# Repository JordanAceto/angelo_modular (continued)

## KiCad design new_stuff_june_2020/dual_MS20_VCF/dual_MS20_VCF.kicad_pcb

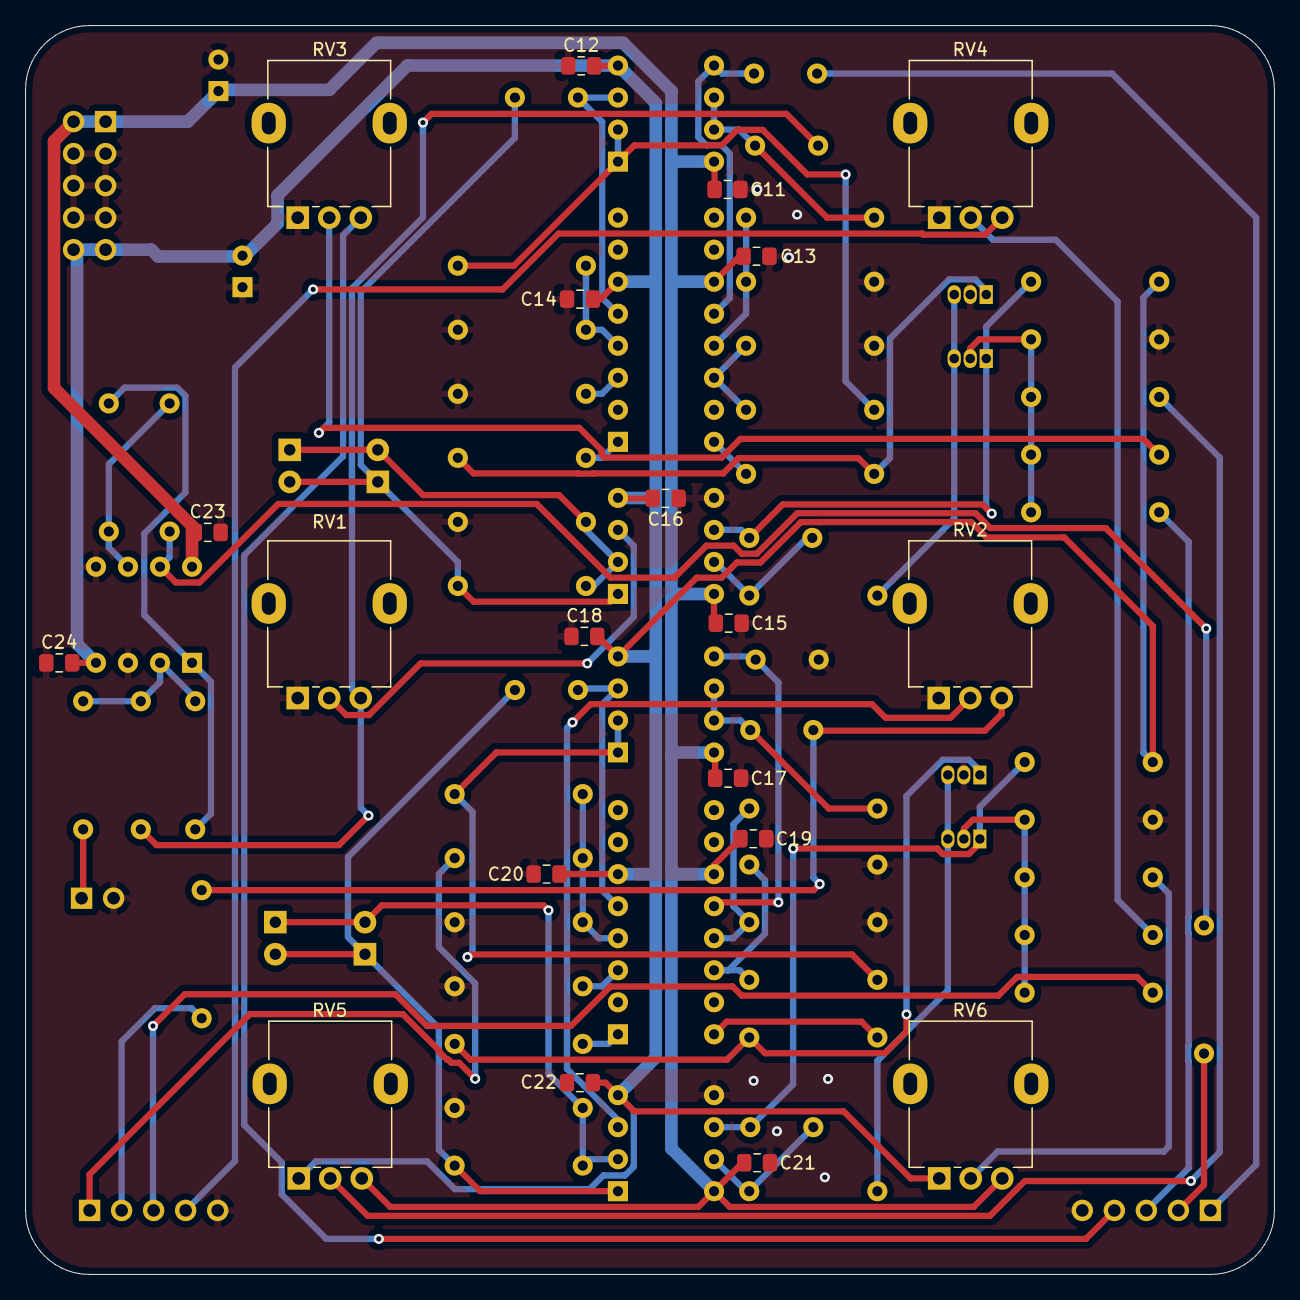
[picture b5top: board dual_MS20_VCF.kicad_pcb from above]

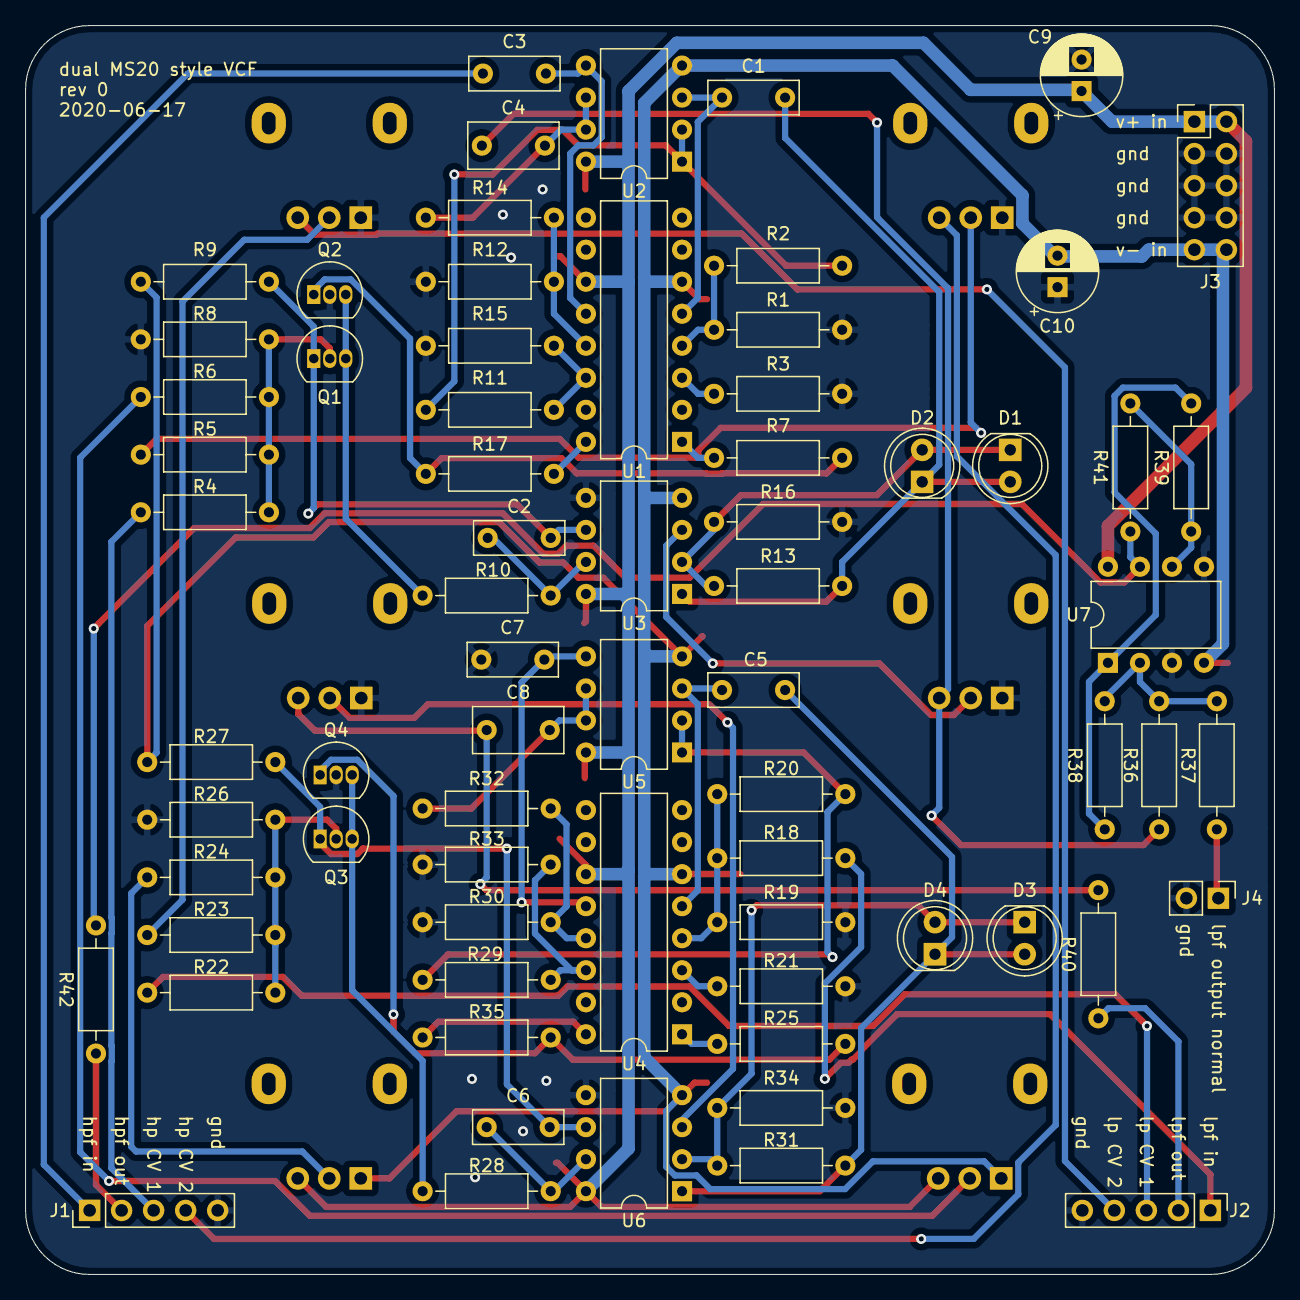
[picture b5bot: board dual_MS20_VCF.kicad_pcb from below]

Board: 2 copper layers, 99.1 x 99.1 mm, 91 parts (71 on the bottom side), 58 nets.

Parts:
C1, C3, C5, C7: 1nF; C_Rect_L7.0mm_W2.5mm_P5.00mm
C2, C6: 4n7; C_Rect_L7.0mm_W2.5mm_P5.00mm
C4, C8: 470nF; C_Rect_L7.0mm_W3.5mm_P5.00mm
C9, C10: 10uF; CP_Radial_D6.3mm_P2.50mm
C11, C12, C13, C14, C15, C16, C17, C18, C19, C20, C21, C22, C23, C24: 100nF; C_0805_2012Metric_Pad1.15x1.40mm_HandSolder
D1, D2, D3, D4: green; LED_D5.0mm
J1, J2: Conn_01x05; PinHeader_1x05_P2.54mm_Vertical
J3: power_in; PinHeader_2x05_P2.54mm_Vertical
J4: lpf_output_normal; PinHeader_1x02_P2.54mm_Vertical
Q1, Q2, Q3, Q4: BC558; TO-92_Inline
R1, R3, R12, R15, R19, R21, R30, R33: 220; R_Axial_DIN0207_L6.3mm_D2.5mm_P10.16mm_Horizontal
R2, R7, R11, R13, R14, R17, R18, R20, R25, R29, R31, R32, R35: 10k; R_Axial_DIN0207_L6.3mm_D2.5mm_P10.16mm_Horizontal
R4, R5, R6, R22, R23, R24, R36, R37, R38, R39, R41: 100k; R_Axial_DIN0207_L6.3mm_D2.5mm_P10.16mm_Horizontal
R8, R16, R26, R34: 1k8; R_Axial_DIN0207_L6.3mm_D2.5mm_P10.16mm_Horizontal
R9, R27: 470k; R_Axial_DIN0207_L6.3mm_D2.5mm_P10.16mm_Horizontal
R10, R28: 4k7; R_Axial_DIN0207_L6.3mm_D2.5mm_P10.16mm_Horizontal
R40, R42: 1k; R_Axial_DIN0207_L6.3mm_D2.5mm_P10.16mm_Horizontal
RV1, RV2, RV3, RV4, RV5, RV6: 100k; Potentiometer_Alpha_RD901F-40-00D_Single_Vertical
U1, U4: LM13700; DIP-16_W7.62mm
U2, U3, U5, U6: MC1458; DIP-8_W7.62mm
U7: TL072; DIP-8_W7.62mm

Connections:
+12V: C9.1, C11.1, C13.1, C15.1, C17.1, C19.1, C21.1, C23.1, J3.1, J3.2, RV5.3, RV6.3, U1.11, U2.8, U3.8, U4.11, U5.8, U6.8, U7.8
-12V: C10.2, C12.2, C14.2, C16.2, C18.2, C20.2, C22.2, C24.2, J3.9, J3.10, R9.2, R27.2, RV5.1, RV6.1, U1.6, U2.4, U3.4, U4.6, U5.4, U6.4, U7.4
/HPF/hpf_cv_in_1: J1.3, R4.2
/HPF/hpf_cv_in_2: R5.2, RV3.2
/HPF/hpf_cv_in_3: R6.2, RV5.2
/HPF/hpf_in: C3.2, J1.1
/HPF/i_out: Q2.1, R7.1, R17.1
/LPF/i_out: Q4.1, R25.1, R35.1
/LPF/lpf_cv_in_1: J2.3, R22.2
/LPF/lpf_cv_in_2: R23.2, RV4.2
/LPF/lpf_cv_in_3: R24.2, RV6.2
/LPF/lpf_in: J2.1, R18.2
/LPF/lpf_out: C8.1, R40.2, RV2.3
/high_pass: C4.1, R36.2, RV1.3
/low_pass: J2.2, R40.1
/summed_hp_lp: J1.2, R42.1
GND: C7.2, C9.2, C10.1, C11.2, C12.1, C13.2, C14.1, C15.2, C16.1, C17.2, C18.1, C19.2, C20.1, C21.2, C22.1, C23.2, C24.1, J1.5, J2.5, J3.3, J3.4, J3.5, J3.6, J3.7, J3.8, J4.2, Q2.2, Q4.2, R1.2, R3.2, R8.2, R12.2, R15.2, R16.2, R19.2, R21.2, R26.2, R30.2, R33.2, R34.2, RV1.1, RV2.1, RV3.1, RV4.1, U3.5, U6.5, U7.3, U7.5
unnamed: C1.1, U1.5, U2.3
unnamed: C1.2, D1.2, D2.1, R13.2, U3.1
unnamed: C2.1, R10.1, U3.7
unnamed: C2.2, Q1.1, R9.1, U3.6
unnamed: C3.1, U1.12, U2.5
unnamed: C4.2, R14.1, U2.6, U2.7
unnamed: C5.1, U4.5, U5.3
unnamed: C5.2, D3.2, D4.1, R31.2, U6.1
unnamed: C6.1, R28.1, U6.7
unnamed: C6.2, Q3.1, R27.1, U6.6
unnamed: C7.1, U4.12, U5.5
unnamed: C8.2, R32.1, U5.6, U5.7
unnamed: D1.1, D2.2, R13.1, R16.1, U3.2
unnamed: D3.1, D4.2, R31.1, R34.1, U6.2
unnamed: J1.4, RV3.3
unnamed: J2.4, RV4.3
unnamed: J4.1, R37.2
unnamed: Q1.2, R4.1, R5.1, R6.1, R8.1
unnamed: Q1.3, Q2.3, R10.2
unnamed: Q3.2, R22.1, R23.1, R24.1, R26.1
unnamed: Q3.3, Q4.3, R28.2
unnamed: R1.1, R2.2, U1.4
unnamed: R3.1, U1.3
unnamed: R7.2, U1.1
unnamed: R11.1, R15.1, U1.14
unnamed: R2.1, R11.2, U2.1, U2.2
unnamed: R12.1, R14.2, U1.13
unnamed: R17.2, U1.16
unnamed: R18.1, R19.1, R20.2, U4.4
unnamed: R20.1, R29.2, U5.1, U5.2
unnamed: R21.1, U4.3
unnamed: R25.2, U4.1
unnamed: R29.1, R33.1, U4.14
unnamed: R30.1, R32.2, U4.13
unnamed: R35.2, U4.16
unnamed: R36.1, R37.1, R38.2, U7.2
unnamed: R38.1, R39.2, U7.1
unnamed: R39.1, R41.2, U7.6
unnamed: R41.1, R42.2, U7.7
unnamed: RV1.2, U3.3
unnamed: RV2.2, U6.3

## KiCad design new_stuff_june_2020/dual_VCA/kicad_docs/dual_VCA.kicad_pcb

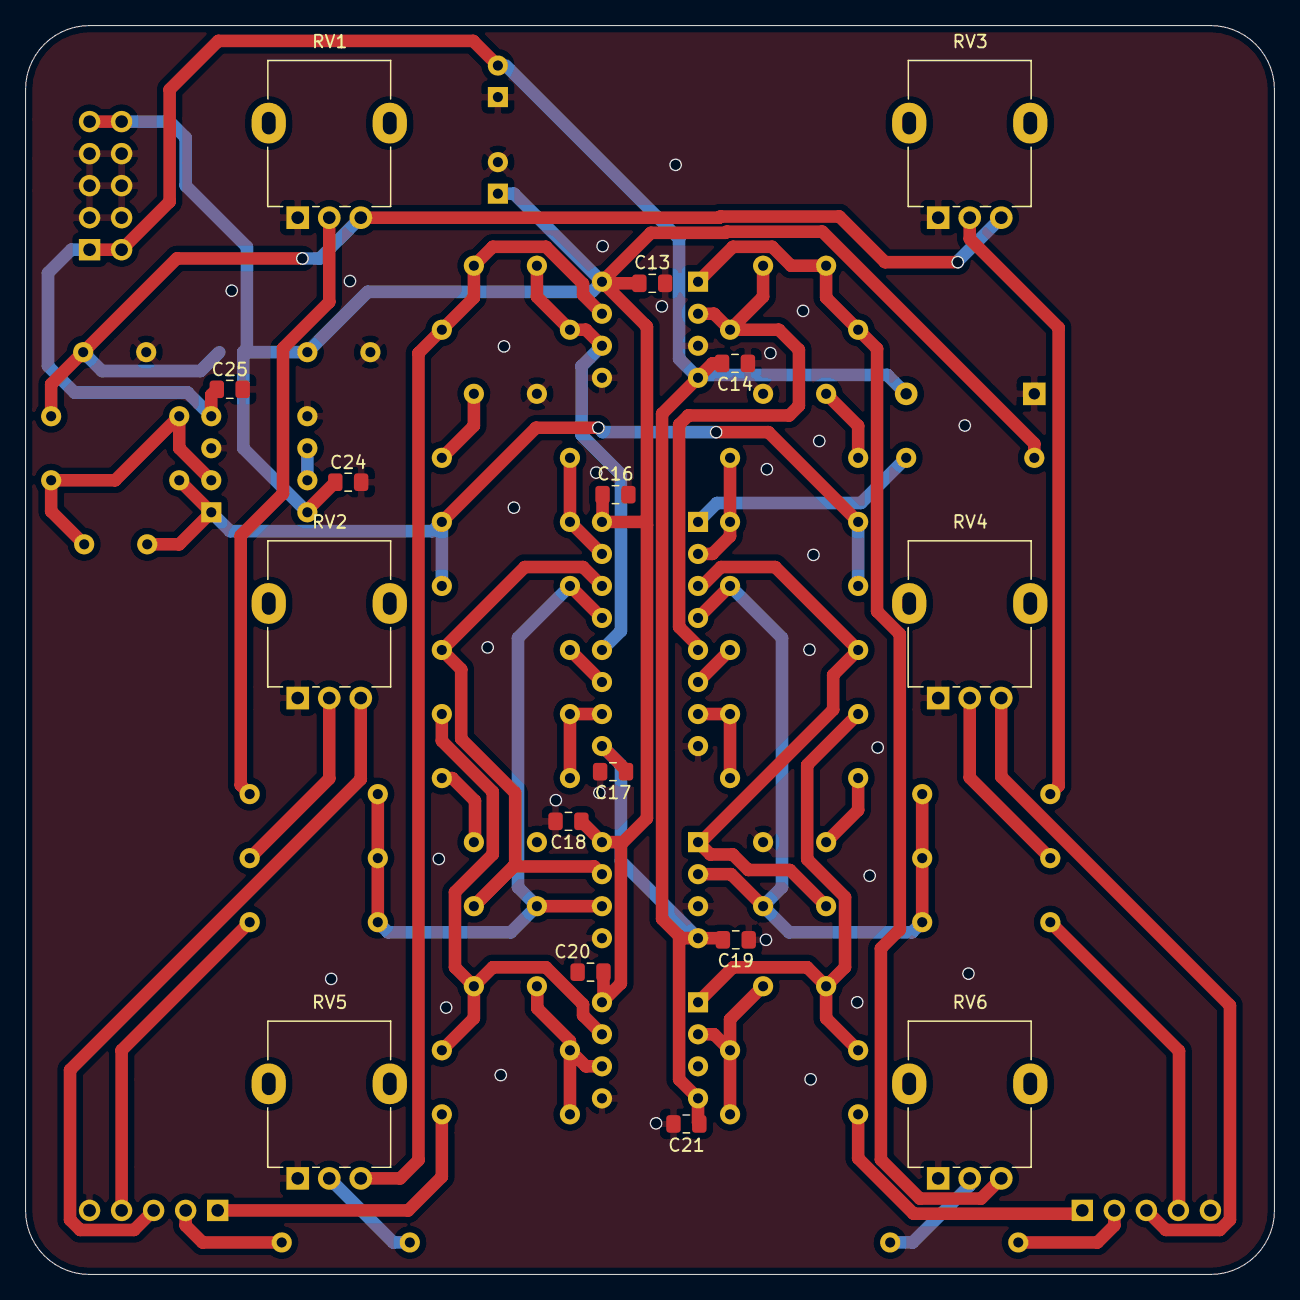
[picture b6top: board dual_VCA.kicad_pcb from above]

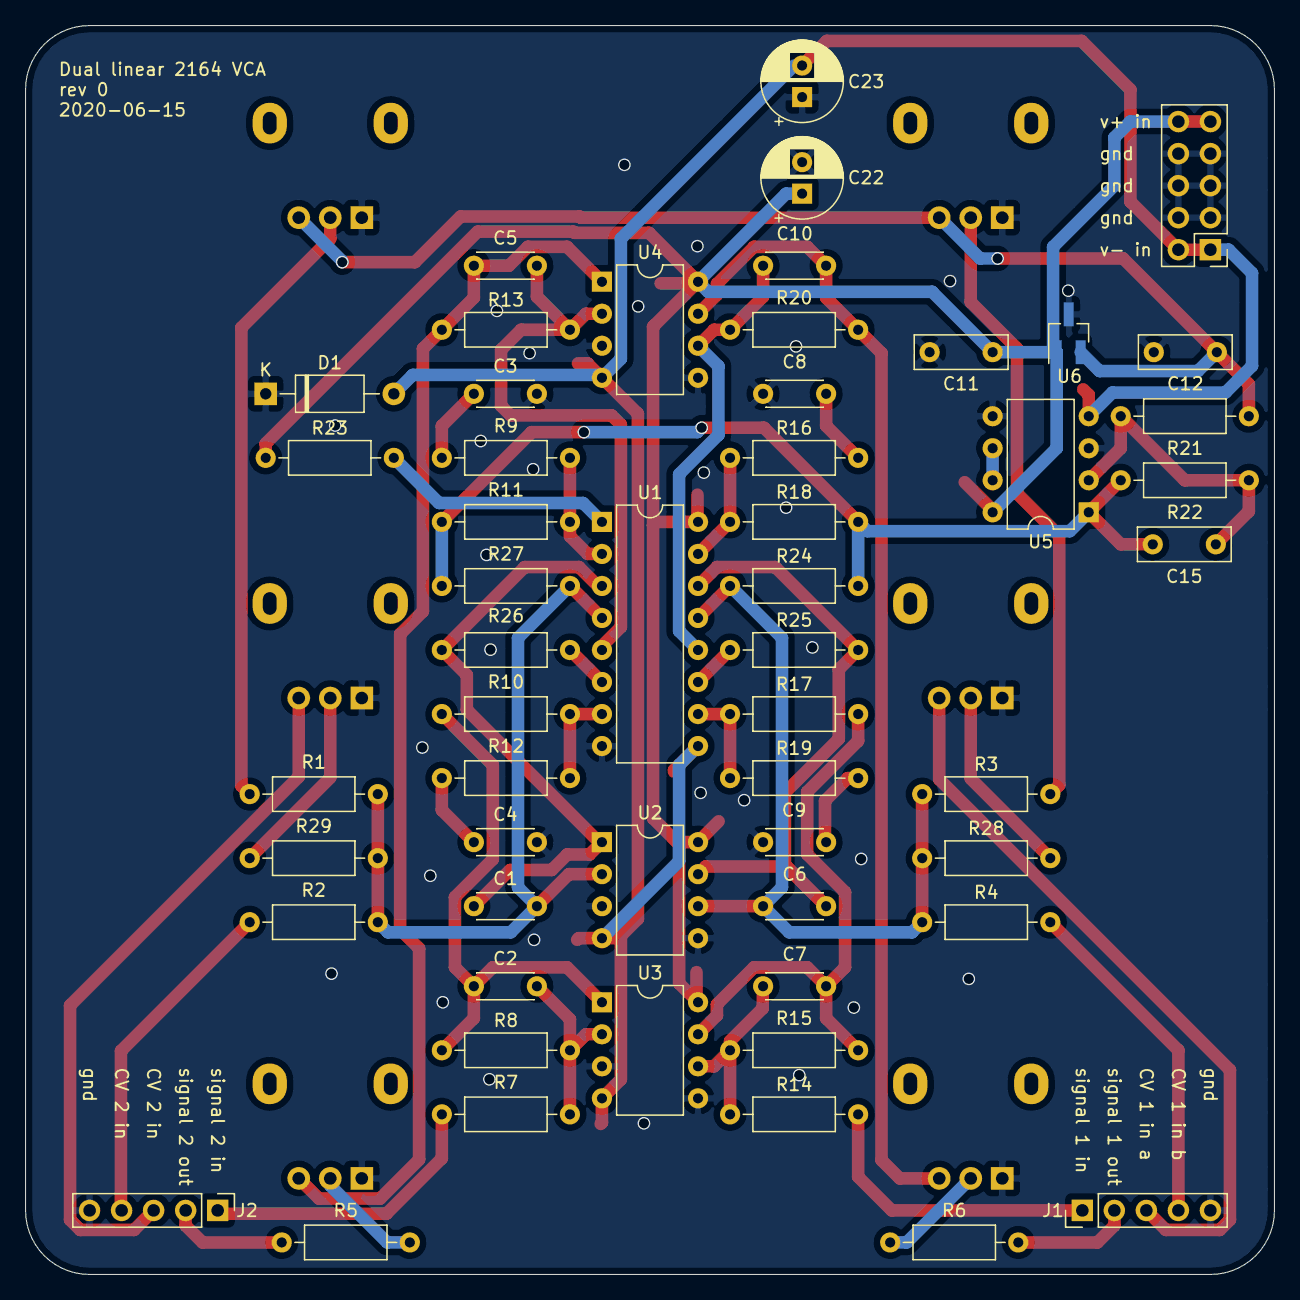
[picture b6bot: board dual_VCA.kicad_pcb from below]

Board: 2 copper layers, 99.1 x 99.1 mm, 70 parts (54 on the bottom side), 44 nets.

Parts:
C1, C5, C6, C10: 100pF; C_Disc_D4.3mm_W1.9mm_P5.00mm
C2, C7: 22pF; C_Disc_D4.3mm_W1.9mm_P5.00mm
C3, C4, C8, C9: 560pF; C_Disc_D4.3mm_W1.9mm_P5.00mm
C11, C12, C15: 100nF; C_Rect_L7.2mm_W2.5mm_P5.00mm_FKS2_FKP2_MKS2_MKP2
C13, C14, C16, C17, C18, C19, C20, C21, C24, C25: 100nF; C_0805_2012Metric_Pad1.15x1.40mm_HandSolder
C22, C23: 10uF; CP_Radial_D6.3mm_P2.50mm
D1: BAT48; D_A-405_P10.16mm_Horizontal
J1: VCA_1_port; PinHeader_1x05_P2.54mm_Vertical
J2: VCA_2_port; PinHeader_1x05_P2.54mm_Vertical
J7: power_input; PinHeader_2x05_P2.54mm_Vertical
R1, R2, R3, R4, R7, R8, R11, R14, R15, R18, R28, R29: 100k; R_Axial_DIN0207_L6.3mm_D2.5mm_P10.16mm_Horizontal
R5, R6: 1k; R_Axial_DIN0207_L6.3mm_D2.5mm_P10.16mm_Horizontal
R9, R12, R16, R19: 510; R_Axial_DIN0207_L6.3mm_D2.5mm_P10.16mm_Horizontal
R10, R13, R17, R20: 30k; R_Axial_DIN0207_L6.3mm_D2.5mm_P10.16mm_Horizontal
R21, R22: 10k; R_Axial_DIN0207_L6.3mm_D2.5mm_P10.16mm_Horizontal
R23: opt; R_Axial_DIN0207_L6.3mm_D2.5mm_P10.16mm_Horizontal
R24, R26: 10M; R_Axial_DIN0207_L6.3mm_D2.5mm_P10.16mm_Horizontal
R25, R27: 4k7; R_Axial_DIN0207_L6.3mm_D2.5mm_P10.16mm_Horizontal
RV1, RV2, RV3, RV4: 100k; Potentiometer_Alpha_RD901F-40-00D_Single_Vertical
RV5, RV6: 10k; Potentiometer_Alpha_RD901F-40-00D_Single_Vertical
U1: SSM2164; DIP-16_W7.62mm
U2, U3, U4, U5: TL072; DIP-8_W7.62mm
U6: MAX6035xxUR50; SOT-23_Handsoldering

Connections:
+5VA: C12.1, R21.2, RV1.3, RV3.3, U6.2
+12V: C11.1, C13.1, C16.1, C18.1, C20.1, C22.1, C24.1, J7.9, J7.10, R23.1, U1.16, U2.8, U3.8, U4.8, U5.8, U6.1
-5VA: C15.1, R11.2, R18.2, R22.1, R24.2, R26.2, U5.1
-12V: C14.2, C17.2, C19.2, C21.2, C23.2, C25.2, D1.2, J7.1, J7.2, U1.9, U2.4, U3.4, U4.4, U5.4
/CV_in_1_A: J1.3, RV2.3
/CV_in_1_B: J1.4, R4.2
/CV_in_2_A: J2.3, RV4.3
/CV_in_2_B: J2.4, R2.2
/VCA_1/VCA_1_CV_summing_node_i_in: C6.2, R3.1, R4.1, R24.1, R28.1, U1.13, U2.6
/VCA_1/VCA_1_signal_v_out: C10.1, R20.1, RV5.3, U4.7
/VCA_2/VCA_2_CV_summing_node_i_in: C1.2, R1.1, R2.1, R26.1, R29.1, U1.4, U2.2
/VCA_2/VCA_2_signal_v_out: C5.1, R13.1, RV6.3, U4.1
/signal_in_1: J1.1, R14.2
/signal_in_2: J2.1, R7.2
/signal_out_1: J1.2, R6.1
/signal_out_2: J2.2, R5.1
GND: C3.2, C4.2, C8.2, C9.2, C11.2, C12.2, C13.2, C14.1, C16.2, C17.1, C18.2, C19.1, C20.2, C21.1, C22.2, C23.1, C24.2, C25.1, D1.1, J1.5, J2.5, J7.3, J7.4, J7.5, J7.6, J7.7, J7.8, RV1.1, RV2.1, RV3.1, RV4.1, RV5.1, RV6.1, U1.8, U2.3, U2.5, U3.3, U3.5, U4.3, U4.5, U5.3, U5.5, U6.3
unnamed: C1.1, R27.2, U1.3, U2.1
unnamed: C2.1, R8.1, R10.2, U3.1
unnamed: C2.2, R7.1, R8.2, U3.2
unnamed: C3.1, R9.2
unnamed: C4.1, R12.2
unnamed: C5.2, R13.2, U1.5, U4.2
unnamed: C6.1, R25.2, U1.14, U2.7
unnamed: C7.1, R15.1, R17.2, U3.7
unnamed: C7.2, R14.1, R15.2, U3.6
unnamed: C8.1, R16.2
unnamed: C9.1, R19.2
unnamed: C10.2, R20.2, U1.12, U4.6
unnamed: C15.2, R21.1, R22.2, U5.2
unnamed: R1.2, RV3.2
unnamed: R3.2, RV1.2
unnamed: R5.2, RV6.2
unnamed: R6.2, RV5.2
unnamed: R10.1, R12.1, U1.7
unnamed: R9.1, R11.1, U1.2
unnamed: R16.1, R18.1, U1.15
unnamed: R17.1, R19.1, U1.10
unnamed: R23.2, U1.1
unnamed: R25.1, U1.11
unnamed: R27.1, U1.6
unnamed: R28.2, RV2.2
unnamed: R29.2, RV4.2
unnamed: U5.6, U5.7
